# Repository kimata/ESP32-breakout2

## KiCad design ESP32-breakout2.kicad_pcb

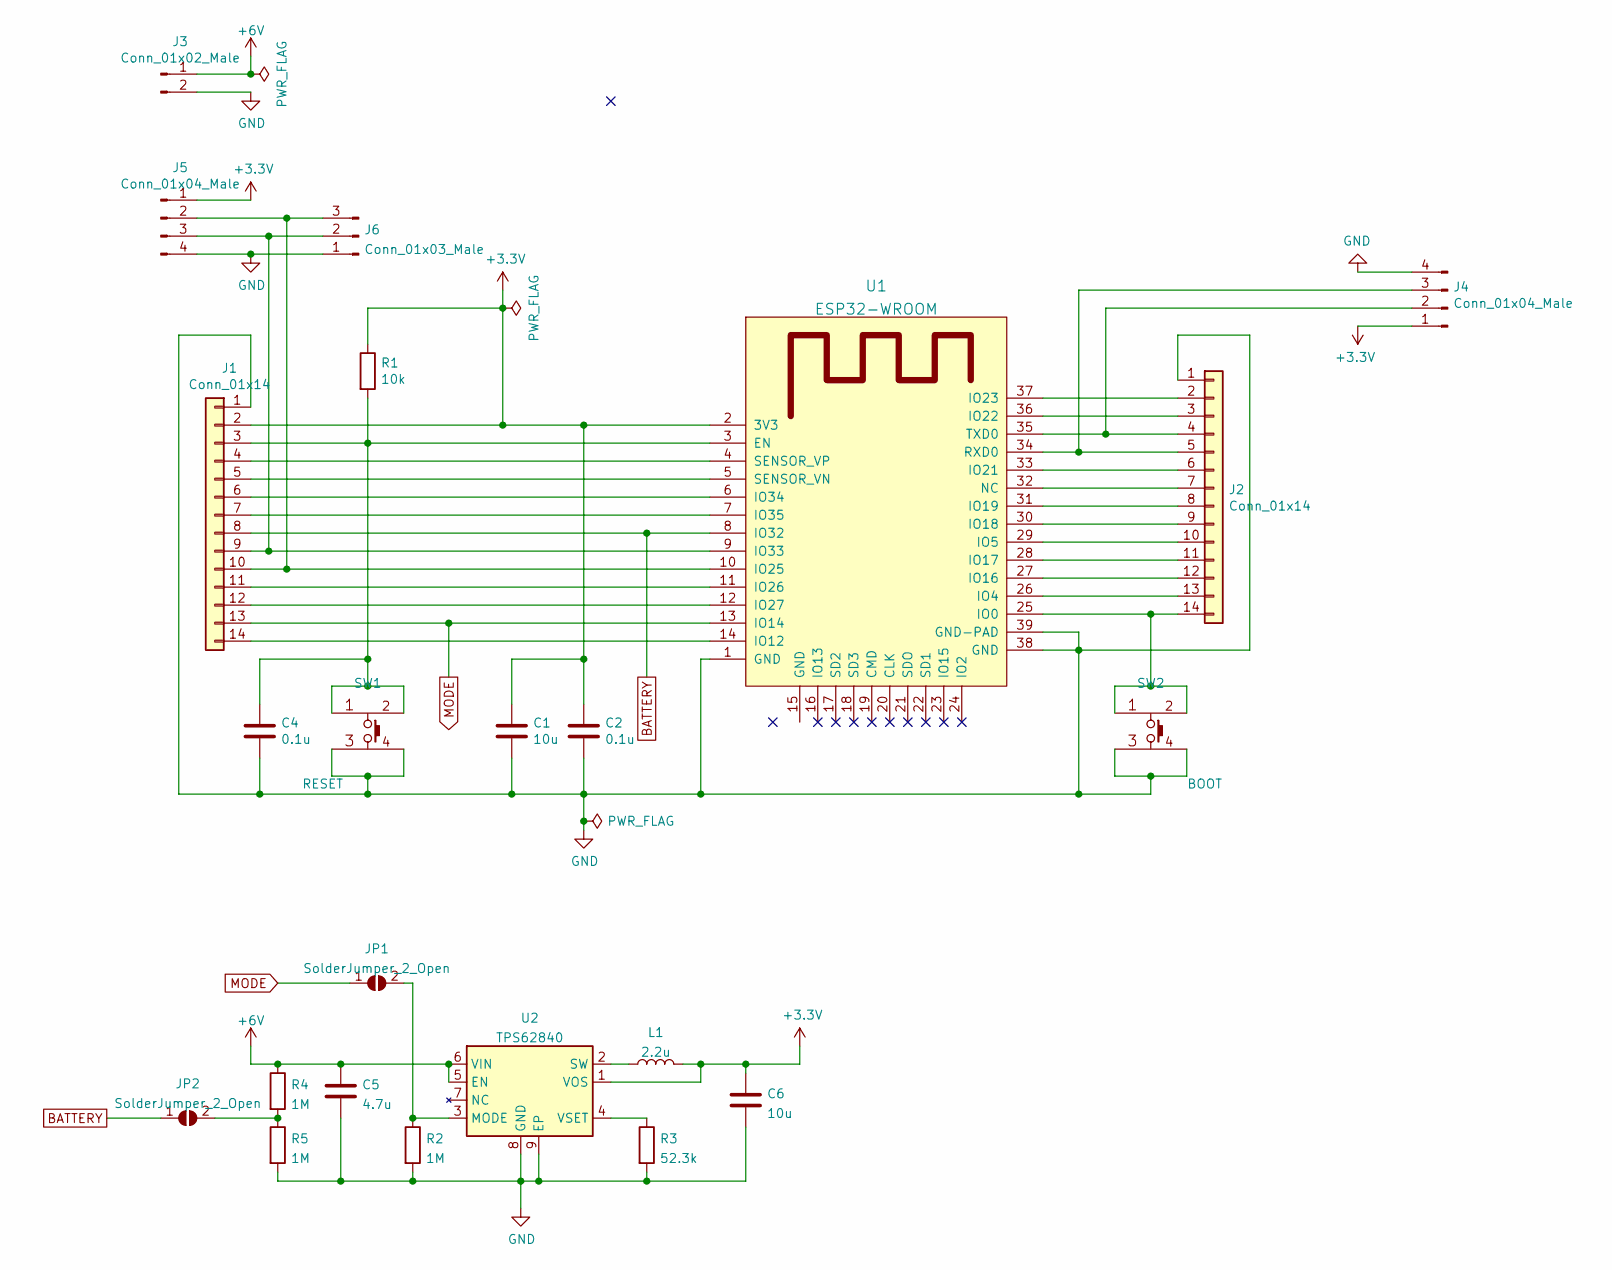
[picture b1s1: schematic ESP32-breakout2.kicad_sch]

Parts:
C1, C6: 10u; C_0805_2012Metric_Pad1.18x1.45mm_HandSolder
C2, C4: 0.1u; C_0805_2012Metric_Pad1.18x1.45mm_HandSolder
C5: 4.7u; C_1206_3216Metric_Pad1.33x1.80mm_HandSolder
J1, J2: Conn_01x14; PinHeader_1x14_P2.54mm_Vertical
J3: Conn_01x02_Male; JST_PH_S2B-PH-SM4-TB_1x02-1MP_P2.00mm_Horizontal
J4, J5: Conn_01x04_Male; JST_PH_S4B-PH-SM4-TB_1x04-1MP_P2.00mm_Horizontal
J6: Conn_01x03_Male; PinHeader_1x03_P2.54mm_Vertical
JP1, JP2: SolderJumper_2_Open; SolderJumper-2_P1.3mm_Open_RoundedPad1.0x1.5mm
L1: 2.2u; VLCF5028T-1R8N2R2-2
R1: 10k; R_0805_2012Metric_Pad1.20x1.40mm_HandSolder
R2, R4, R5: 1M; R_0805_2012Metric_Pad1.20x1.40mm_HandSolder
R3: 52.3k; R_0805_2012Metric_Pad1.20x1.40mm_HandSolder
SW1: RESET; SKRPACE010
SW2: BOOT; SKRPACE010
U1: ESP32-WROOM
U2: TPS62840; VSSOP-8_3.0x3.0mm_P0.65mm_withPAD

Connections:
+3V3: C1.1, C2.1, C6.1, J1.2, J4.1, J5.1, L1.2, R1.1, U1.2 (3V3), U2.1 (VOS)
+6V: C5.1, J3.1, R4.1, U2.5 (EN), U2.6 (VIN)
BATTERY: J1.8, JP2.1 (A), U1.8 (IO32)
GND: C1.2, C2.2, C4.2, C5.2, C6.2, J1.1, J2.1, J3.2, J4.4, J5.4, J6.1, R2.2, R3.2, R5.2, SW1.3, SW1.4, SW2.3, SW2.4, U1.1 (GND), U1.38 (GND), U1.39 (GND-PAD), U2.8 (GND), U2.9 (EP)
MODE: J1.13, JP1.1 (A), U1.13 (IO14)
unnamed: C4.1, J1.3, R1.2, SW1.1, SW1.2, U1.3 (EN)
unnamed: J1.4, U1.4 (SENSOR_VP)
unnamed: J1.5, U1.5 (SENSOR_VN)
unnamed: J1.6, U1.6 (IO34)
unnamed: J1.7, U1.7 (IO35)
unnamed: J1.9, J5.3, J6.2, U1.9 (IO33)
unnamed: J1.10, J5.2, J6.3, U1.10 (IO25)
unnamed: J1.11, U1.11 (IO26)
unnamed: J1.12, U1.12 (IO27)
unnamed: J1.14, U1.14 (IO12)
unnamed: J2.2, U1.37 (IO23)
unnamed: J2.3, U1.36 (IO22)
unnamed: J2.4, J4.2, U1.35 (TXD0)
unnamed: J2.5, J4.3, U1.34 (RXD0)
unnamed: J2.6, U1.33 (IO21)
unnamed: J2.7, U1.32 (NC)
unnamed: J2.8, U1.31 (IO19)
unnamed: J2.9, U1.30 (IO18)
unnamed: J2.10, U1.29 (IO5)
unnamed: J2.11, U1.28 (IO17)
unnamed: J2.12, U1.27 (IO16)
unnamed: J2.13, U1.26 (IO4)
unnamed: J2.14, SW2.1, SW2.2, U1.25 (IO0)
unnamed: JP1.2 (B), R2.1, U2.3 (MODE)
unnamed: L1.1, U2.2 (SW)
unnamed: R3.1, U2.4 (VSET)
unnamed: JP2.2 (B), R4.2, R5.1

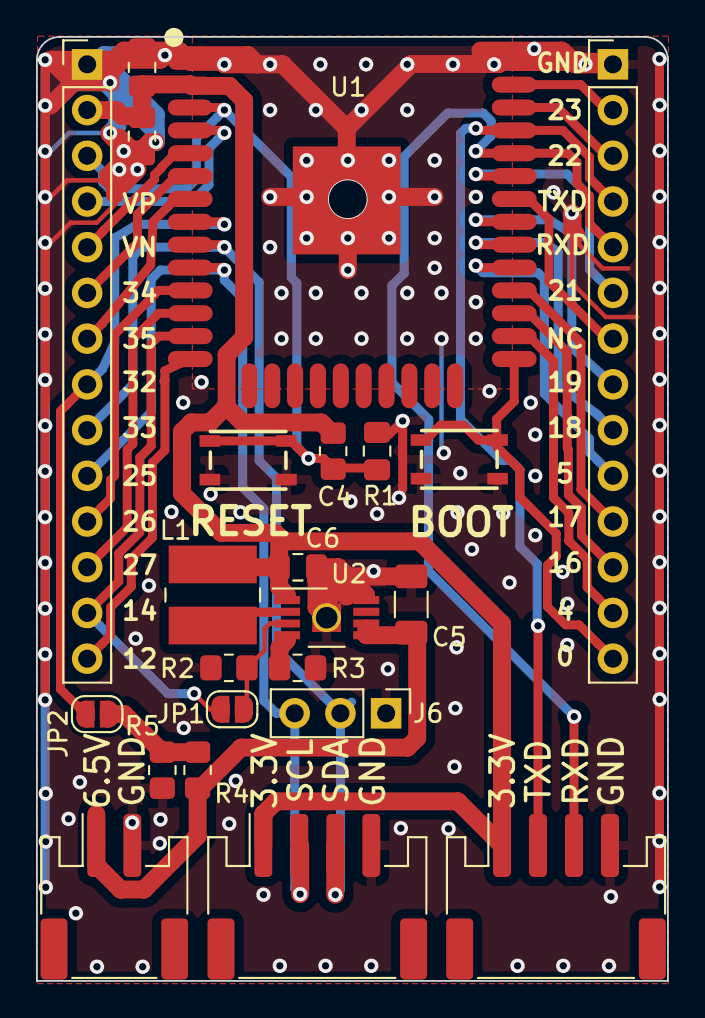
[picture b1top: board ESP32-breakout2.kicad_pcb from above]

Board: 2 copper layers, 35.1 x 52.4 mm, 23 parts (0 on the bottom side), 32 nets.

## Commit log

2021-10-22 feat: とりあえず完成
2023-12-15 Add renovate.json

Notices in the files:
parts and their libraries:
Copyright 2021 Accelerated Designs. All rights reserved.
